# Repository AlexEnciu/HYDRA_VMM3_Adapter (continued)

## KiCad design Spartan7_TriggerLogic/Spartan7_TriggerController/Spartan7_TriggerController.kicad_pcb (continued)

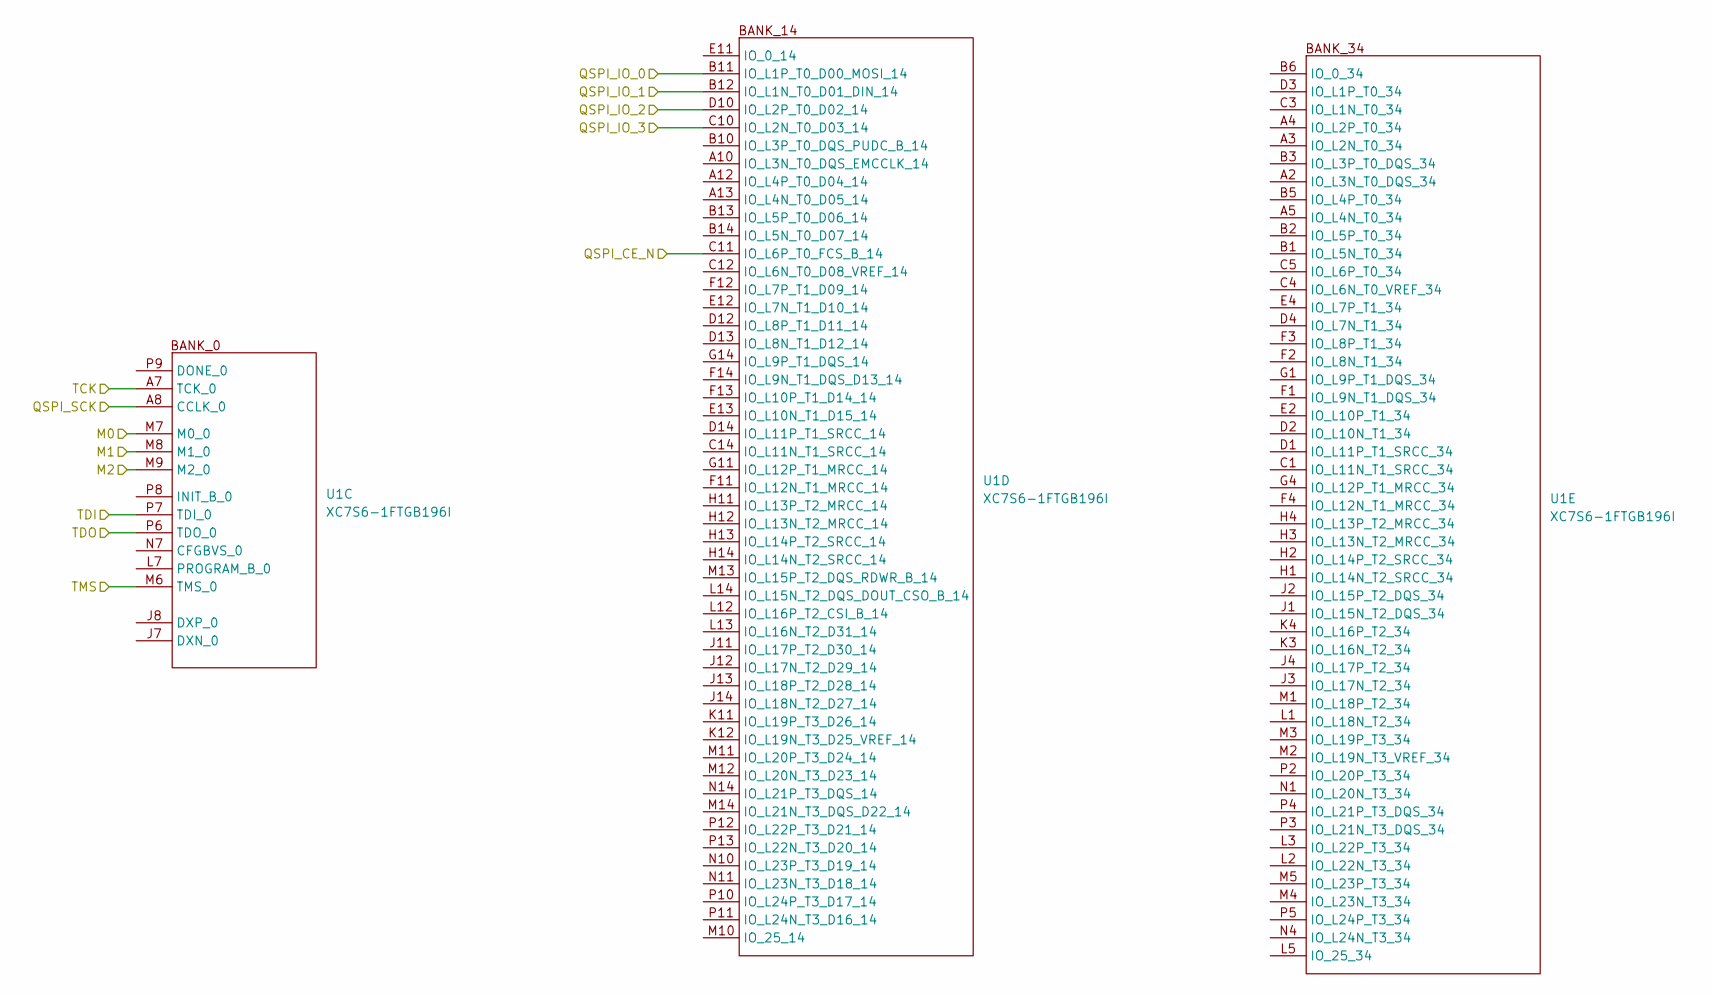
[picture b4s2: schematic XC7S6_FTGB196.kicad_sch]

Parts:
U1: XC7S6-1FTGB196I; BGA196C100P14X14_1500X1500X155N

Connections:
/Boot_Mode/M0: U1.M7 (M0_0); also elsewhere on the board
/Boot_Mode/M1: U1.M8 (M1_0); also elsewhere on the board
/Boot_Mode/M2: U1.M9 (M2_0); also elsewhere on the board
/JTAG/TCK: U1.A7 (TCK_0); also elsewhere on the board
/JTAG/TDI: U1.P7 (TDI_0); also elsewhere on the board
/JTAG/TDO: U1.P6 (TDO_0); also elsewhere on the board
/JTAG/TMS: U1.M6 (TMS_0); also elsewhere on the board
/QSPI/QSPI_CE_N: U1.C11 (IO_L6P_T0_FCS_B_14); also elsewhere on the board
/QSPI/QSPI_IO_0: U1.B11 (IO_L1P_T0_D00_MOSI_14); also elsewhere on the board
/QSPI/QSPI_IO_1: U1.B12 (IO_L1N_T0_D01_DIN_14); also elsewhere on the board
/QSPI/QSPI_IO_2: U1.D10 (IO_L2P_T0_D02_14); also elsewhere on the board
/QSPI/QSPI_IO_3: U1.C10 (IO_L2N_T0_D03_14); also elsewhere on the board
/QSPI/QSPI_SCK: U1.A8 (CCLK_0); also elsewhere on the board

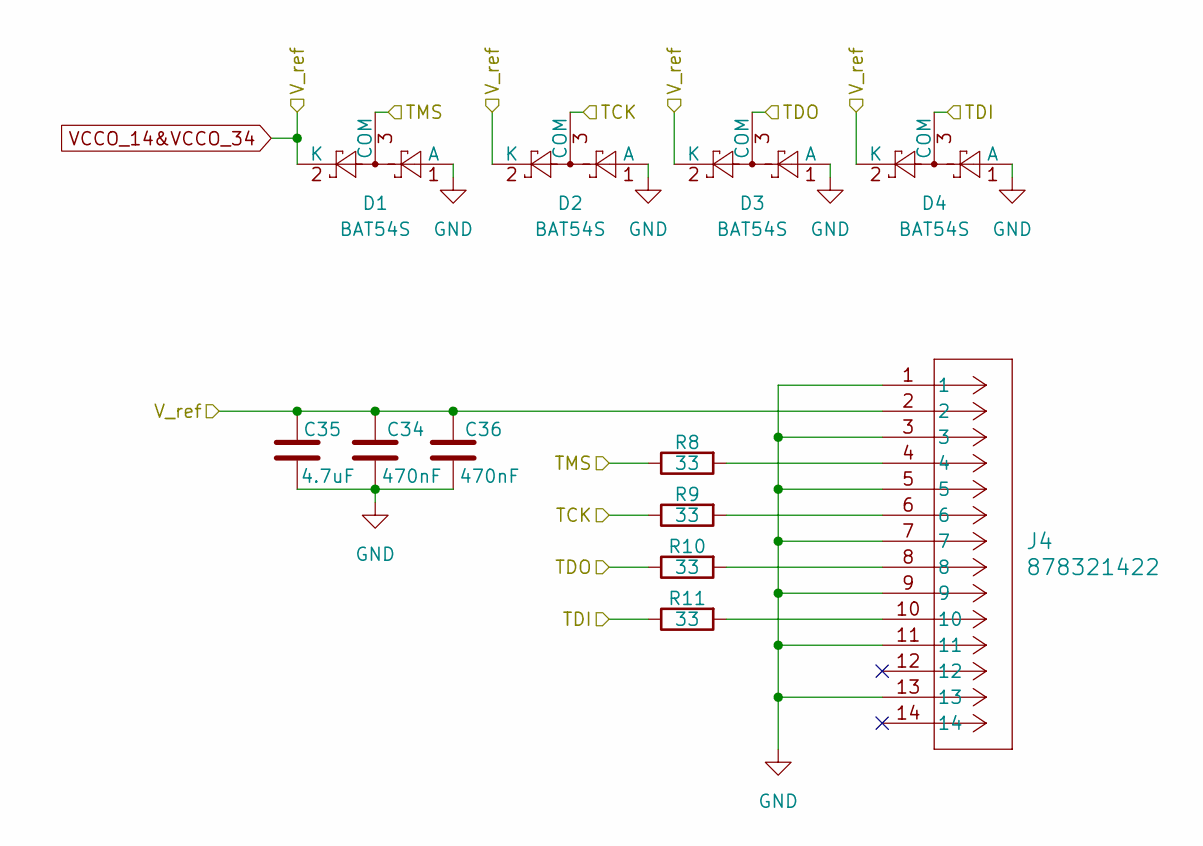
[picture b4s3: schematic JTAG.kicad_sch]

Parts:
C34, C36: 470nF; C_0402_1005Metric
C35: 4.7uF; C_0603_1608Metric
D1, D2, D3, D4: BAT54S; SOT-23
J4: 878321422; CONN14_878321422_MOL
R8, R9, R10, R11: 33; R_0402_1005Metric

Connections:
/JTAG/TCK: D2.3 (COM), R9.1; also elsewhere on the board
/JTAG/TDI: D4.3 (COM), R11.1; also elsewhere on the board
/JTAG/TDO: D3.3 (COM), R10.1; also elsewhere on the board
/JTAG/TMS: D1.3 (COM), R8.1; also elsewhere on the board
GND: C34.2, C35.2, C36.2, D1.1 (A), D2.1 (A), D3.1 (A), D4.1 (A), J4.1, J4.3, J4.5, J4.7, J4.9, J4.11, J4.13; also elsewhere on the board
unnamed: J4.4, R8.2
unnamed: J4.6, R9.2
unnamed: J4.8, R10.2
unnamed: J4.10, R11.2
VCCO_14&VCCO_34: C34.1, C35.1, C36.1, D1.2 (K), D2.2 (K), D3.2 (K), D4.2 (K), J4.2; also elsewhere on the board

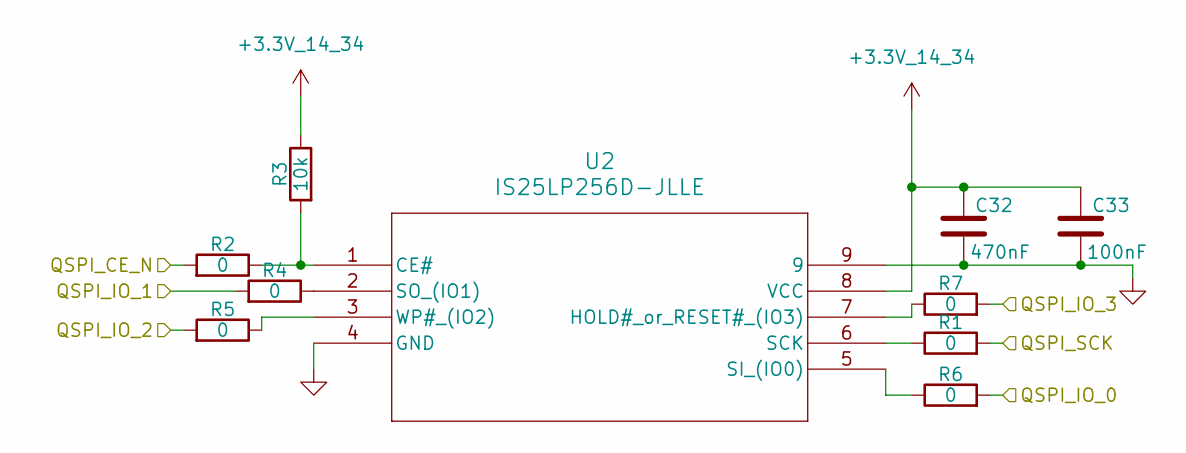
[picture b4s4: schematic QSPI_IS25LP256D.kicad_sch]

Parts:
C32: 470nF; C_0402_1005Metric
C33: 100nF; C_0402_1005Metric
R1, R2, R4, R5, R6, R7: 0; R_0402_1005Metric
R3: 10k; R_0402_1005Metric
U2: IS25LP256D-JLLE; WSON_6D-JLLE_ISI

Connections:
/QSPI/QSPI_CE_N: R2.2; also elsewhere on the board
/QSPI/QSPI_IO_0: R6.2; also elsewhere on the board
/QSPI/QSPI_IO_1: R4.2; also elsewhere on the board
/QSPI/QSPI_IO_2: R5.2; also elsewhere on the board
/QSPI/QSPI_IO_3: R7.2; also elsewhere on the board
/QSPI/QSPI_SCK: R1.2; also elsewhere on the board
GND: C32.2, C33.2, U2.4 (GND), U2.9; also elsewhere on the board
unnamed: R2.1, R3.2, U2.1 (CE#)
unnamed: R7.1, U2.7 (HOLD#_or_RESET#_(IO3))
unnamed: R1.1, U2.6 (SCK)
unnamed: R6.1, U2.5 (SI_(IO0))
unnamed: R4.1, U2.2 (SO_(IO1))
unnamed: R5.1, U2.3 (WP#_(IO2))
VCCO_14&VCCO_34: C32.1, C33.1, R3.1, U2.8 (VCC); also elsewhere on the board

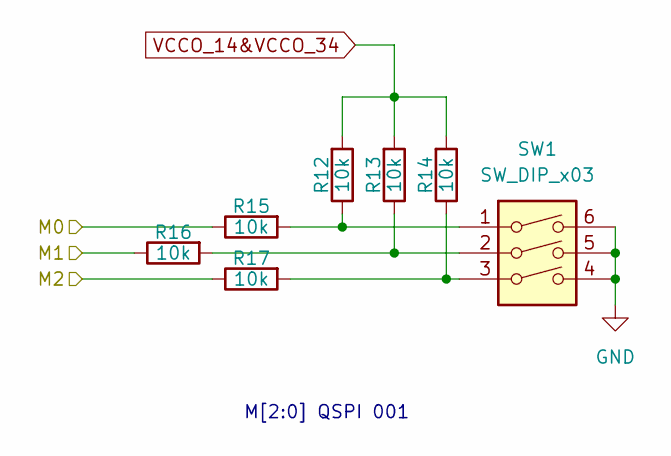
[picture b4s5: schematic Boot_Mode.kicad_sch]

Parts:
R12, R13, R14, R15, R16, R17: 10k; R_0402_1005Metric
SW1: SW_DIP_x03; SW_DIP_SPSTx03_Slide_6.7x9.18mm_W6.73mm_P2.54mm_LowProfile_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

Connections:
/Boot_Mode/M0: R15.1; also elsewhere on the board
/Boot_Mode/M1: R16.1; also elsewhere on the board
/Boot_Mode/M2: R17.1; also elsewhere on the board
GND: SW1.4, SW1.5, SW1.6; also elsewhere on the board
unnamed: R12.1, R15.2, SW1.1
unnamed: R13.1, R16.2, SW1.2
unnamed: R14.1, R17.2, SW1.3
VCCO_14&VCCO_34: R12.2, R13.2, R14.2; also elsewhere on the board

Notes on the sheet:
M[2:0] QSPI 001

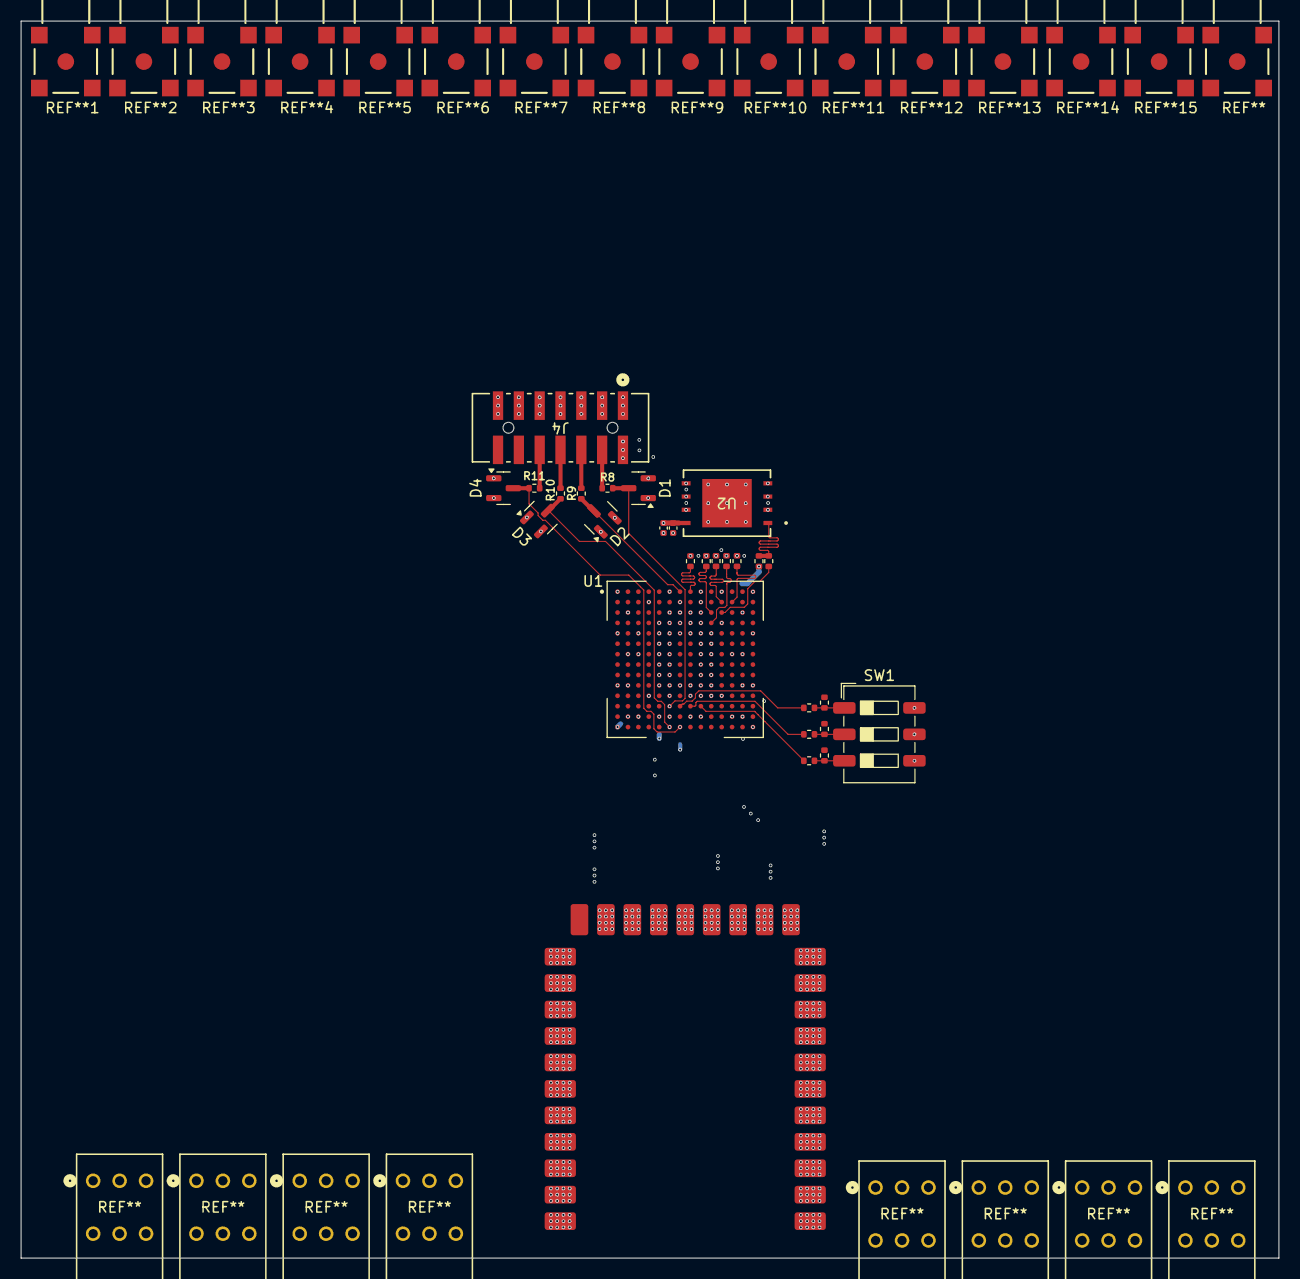
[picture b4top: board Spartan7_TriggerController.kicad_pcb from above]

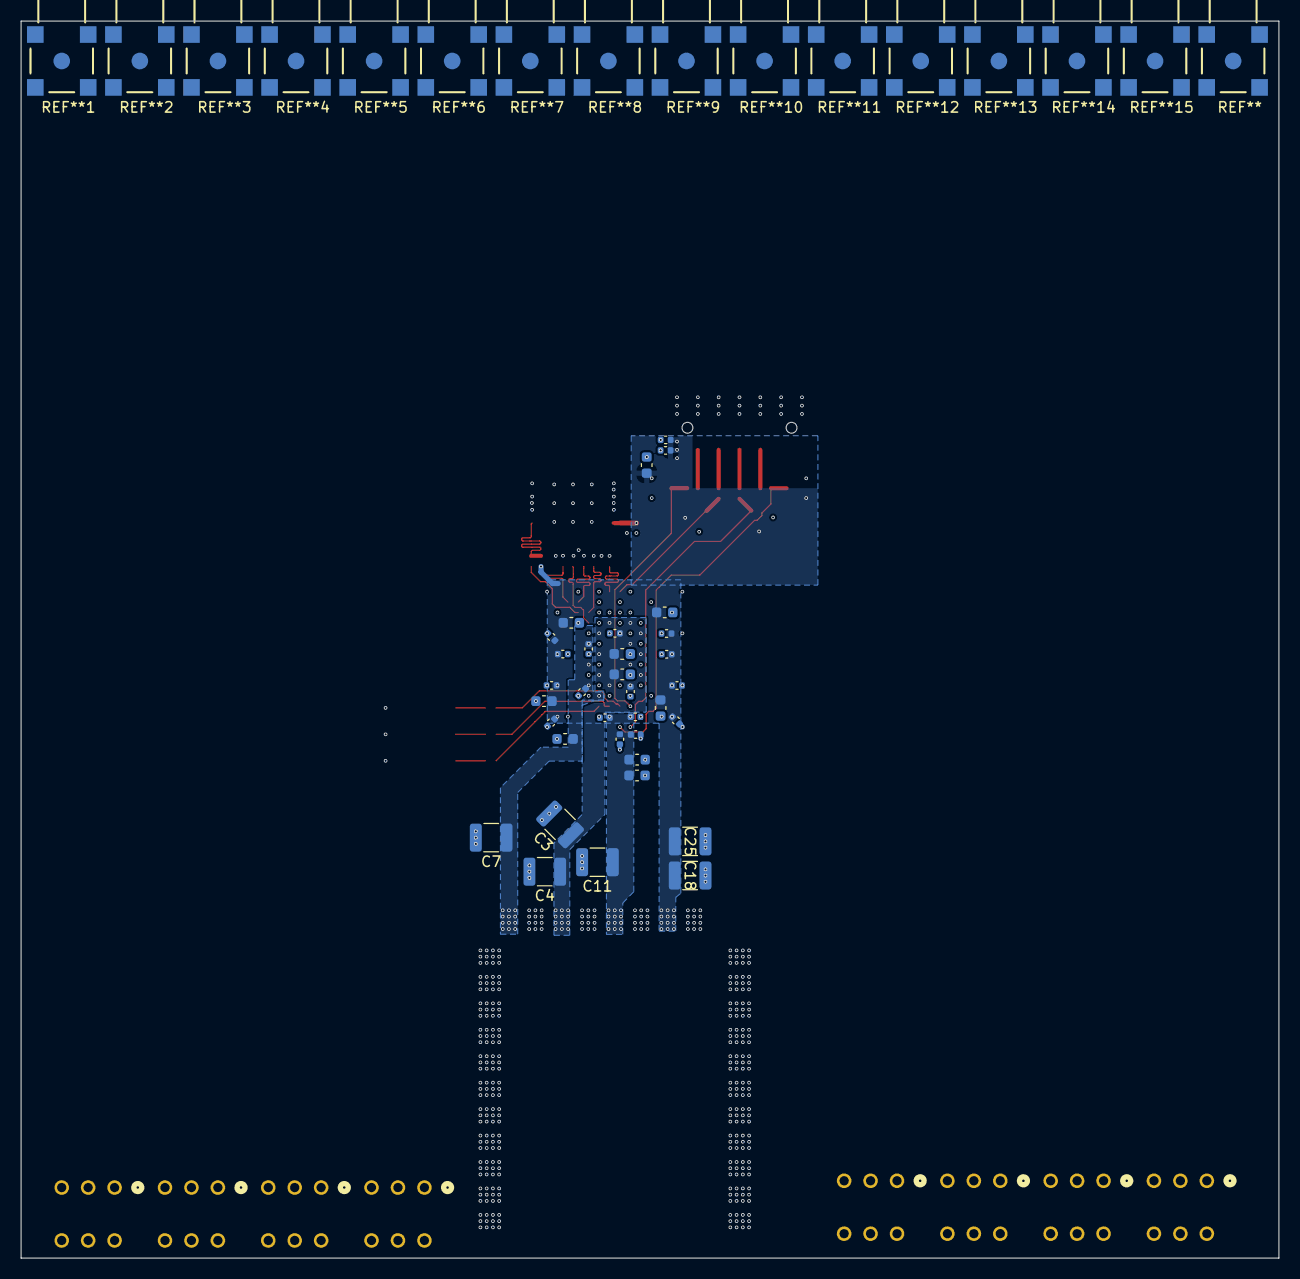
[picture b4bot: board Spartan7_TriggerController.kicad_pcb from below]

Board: 6 copper layers, 120.8 x 118.8 mm, 64 parts (34 on the bottom side), 31 nets.

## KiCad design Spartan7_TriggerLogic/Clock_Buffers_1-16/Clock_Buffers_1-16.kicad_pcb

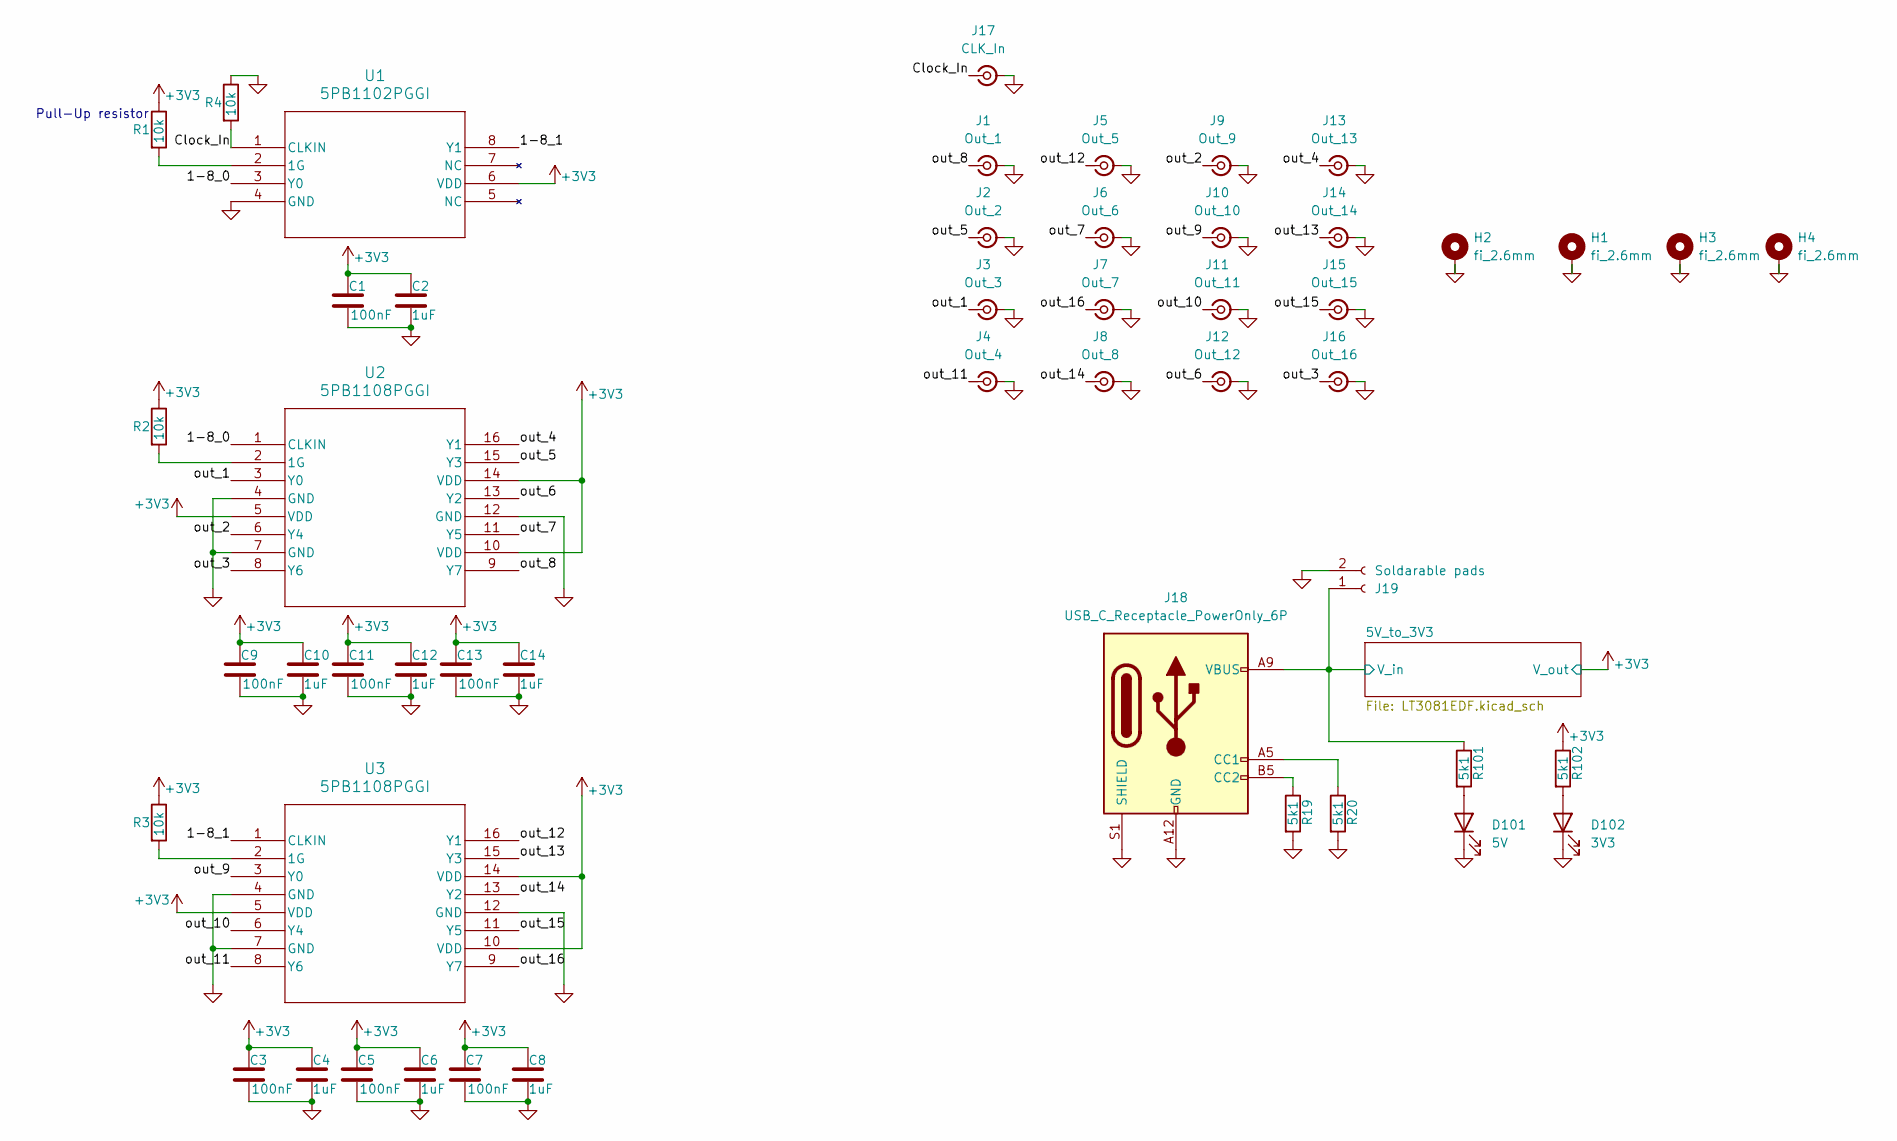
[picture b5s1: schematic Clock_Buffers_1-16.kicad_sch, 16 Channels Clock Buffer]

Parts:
C1, C3, C5, C7, C9, C11, C13: 100nF; C_0402_1005Metric
C2, C4, C6, C8, C10, C12, C14: 1uF; C_0402_1005Metric
D101: 5V; LED_0603_1608Metric
D102: 3V3; LED_0603_1608Metric
H1, H2, H3, H4: fi_2.6mm; MountingHole_2.7mm_M2.5_Pad_Via
J1: Out_1; LINX_CONMCX002-SMD-T
J2: Out_2; LINX_CONMCX002-SMD-T
J3: Out_3; LINX_CONMCX002-SMD-T
J4: Out_4; LINX_CONMCX002-SMD-T
J5: Out_5; LINX_CONMCX002-SMD-T
J6: Out_6; LINX_CONMCX002-SMD-T
J7: Out_7; LINX_CONMCX002-SMD-T
J8: Out_8; LINX_CONMCX002-SMD-T
J9: Out_9; LINX_CONMCX002-SMD-T
J10: Out_10; LINX_CONMCX002-SMD-T
J11: Out_11; LINX_CONMCX002-SMD-T
J12: Out_12; LINX_CONMCX002-SMD-T
J13: Out_13; LINX_CONMCX002-SMD-T
J14: Out_14; LINX_CONMCX002-SMD-T
J15: Out_15; LINX_CONMCX002-SMD-T
J16: Out_16; LINX_CONMCX002-SMD-T
J17: CLK_In; LINX_CONMCX002-SMD-T
J18: USB_C_Receptacle_PowerOnly_6P; CONN6_USB4125_GCT
J19: Soldarable pads; JST_PH_S2B-PH-K_1x02_P2.00mm_Horizontal
R1, R2, R3, R4: 10k; R_0402_1005Metric
R19, R20, R101, R102: 5k1; R_0402_1005Metric
U1: 5PB1102PGGI
U2, U3: 5PB1108PGGI; 5PB1108PGGI_REN

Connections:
+3V3: C1.1, C2.1, C3.1, C4.1, C5.1, C6.1, C7.1, C8.1, C9.1, C10.1, C11.1, C12.1, C13.1, C14.1, R1.1, R2.1, R3.1, R102.1, U1.6 (VDD), U2.5 (VDD), U2.10 (VDD), U2.14 (VDD), U3.5 (VDD), U3.10 (VDD), U3.14 (VDD); also elsewhere on the board
/1-8_0: U1.3 (Y0), U2.1 (CLKIN)
/1-8_1: U1.8 (Y1), U3.1 (CLKIN)
/5V_to_3V3/V_in: J18.A9 (VBUS), J18.B9 (VBUS), J19.1, R101.1; also elsewhere on the board
/Clock_In: J17.1 (In), R4.2, U1.1 (CLKIN)
/out_1: J3.1 (In), U2.3 (Y0)
/out_2: J9.1 (In), U2.6 (Y4)
/out_3: J16.1 (In), U2.8 (Y6)
/out_4: J13.1 (In), U2.16 (Y1)
/out_5: J2.1 (In), U2.15 (Y3)
/out_6: J12.1 (In), U2.13 (Y2)
/out_7: J6.1 (In), U2.11 (Y5)
/out_8: J1.1 (In), U2.9 (Y7)
/out_9: J10.1 (In), U3.3 (Y0)
/out_10: J11.1 (In), U3.6 (Y4)
/out_11: J4.1 (In), U3.8 (Y6)
/out_12: J5.1 (In), U3.16 (Y1)
/out_13: J14.1 (In), U3.15 (Y3)
/out_14: J8.1 (In), U3.13 (Y2)
/out_15: J15.1 (In), U3.11 (Y5)
/out_16: J7.1 (In), U3.9 (Y7)
GND: C1.2, C2.2, C3.2, C4.2, C5.2, C6.2, C7.2, C8.2, C9.2, C10.2, C11.2, C12.2, C13.2, C14.2, D101.1 (K), D102.1 (K), H1.1, H2.1, H3.1, H4.1, J1.2 (Ext), J2.2 (Ext), J3.2 (Ext), J4.2 (Ext), J5.2 (Ext), J6.2 (Ext), J7.2 (Ext), J8.2 (Ext), J9.2 (Ext), J10.2 (Ext), J11.2 (Ext), J12.2 (Ext), J13.2 (Ext), J14.2 (Ext), J15.2 (Ext), J16.2 (Ext), J17.2 (Ext), J18.A12 (GND), J18.B12 (GND), J18.S1 (SHIELD), J19.2, R4.1, R19.2, R20.2, U1.4 (GND), U2.4 (GND), U2.7 (GND), U2.12 (GND), U3.4 (GND), U3.7 (GND), U3.12 (GND); also elsewhere on the board
unnamed: D101.2 (A), R101.2
unnamed: D102.2 (A), R102.2
unnamed: J18.A5 (CC1), R20.1
unnamed: J18.B5 (CC2), R19.1
unnamed: R1.2, U1.2 (1G)
unnamed: R2.2, U2.2 (1G)
unnamed: R3.2, U3.2 (1G)

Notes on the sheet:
Pull-Up resistor

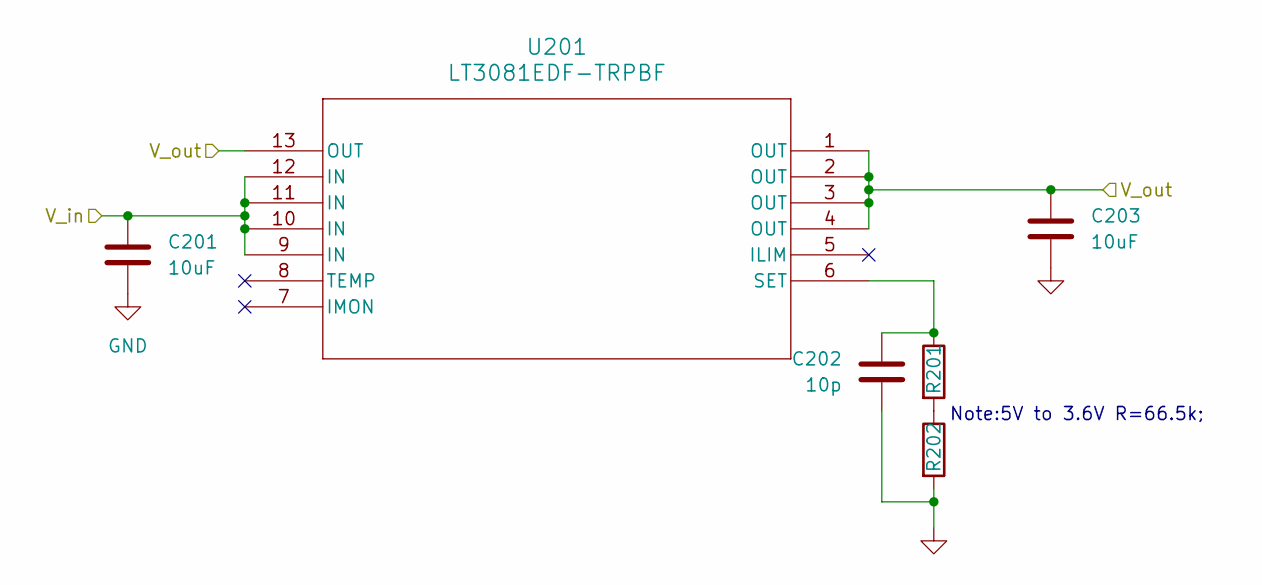
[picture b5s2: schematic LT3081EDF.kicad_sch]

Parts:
C201, C203: 10uF; C_0805_2012Metric
C202: 10p; C_0603_1608Metric
R201, R202: 40k; R_0603_1608Metric
U201: LT3081EDF-TRPBF; DFN-12_DF_LIT

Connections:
+3V3: C203.1, U201.1 (OUT), U201.2 (OUT), U201.3 (OUT), U201.4 (OUT), U201.13 (OUT); also elsewhere on the board
/5V_to_3V3/V_in: C201.1, U201.9 (IN), U201.10 (IN), U201.11 (IN), U201.12 (IN); also elsewhere on the board
GND: C201.2, C202.2, C203.2, R202.2; also elsewhere on the board
unnamed: R201.2, R202.1
unnamed: C202.1, R201.1, U201.6 (SET)

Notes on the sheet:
Note:5V to 3.6V R=66.5k;

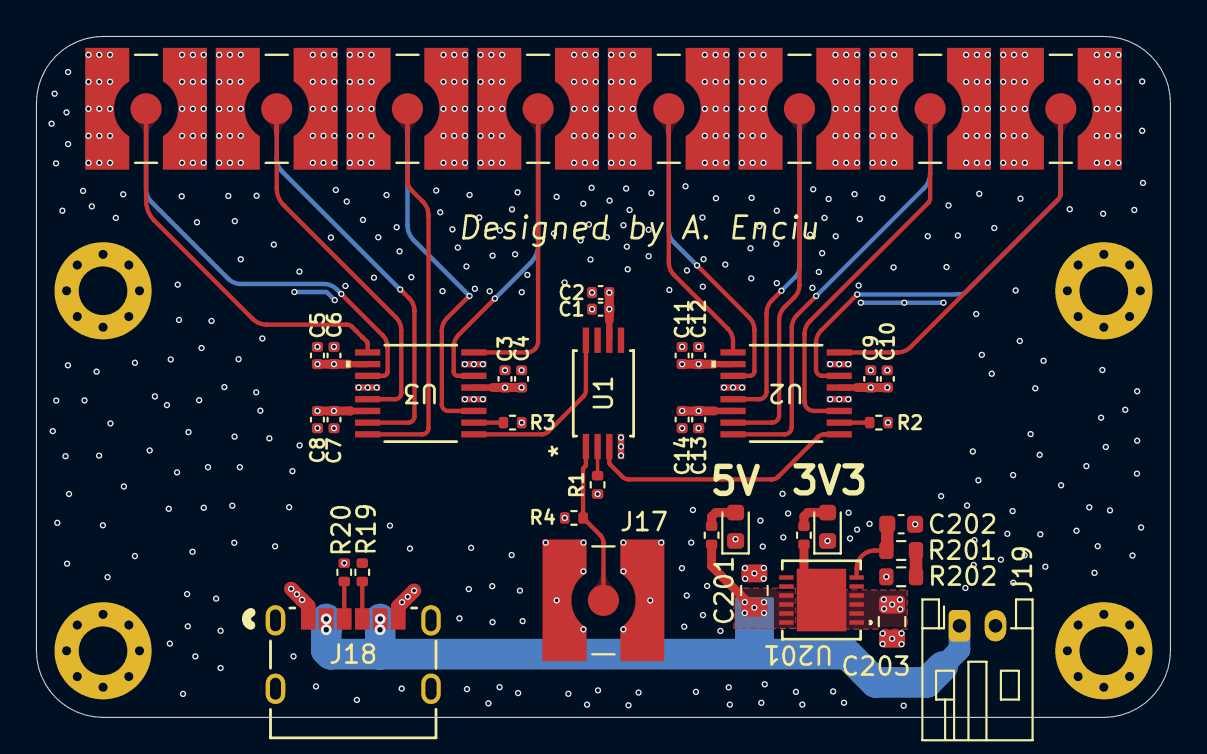
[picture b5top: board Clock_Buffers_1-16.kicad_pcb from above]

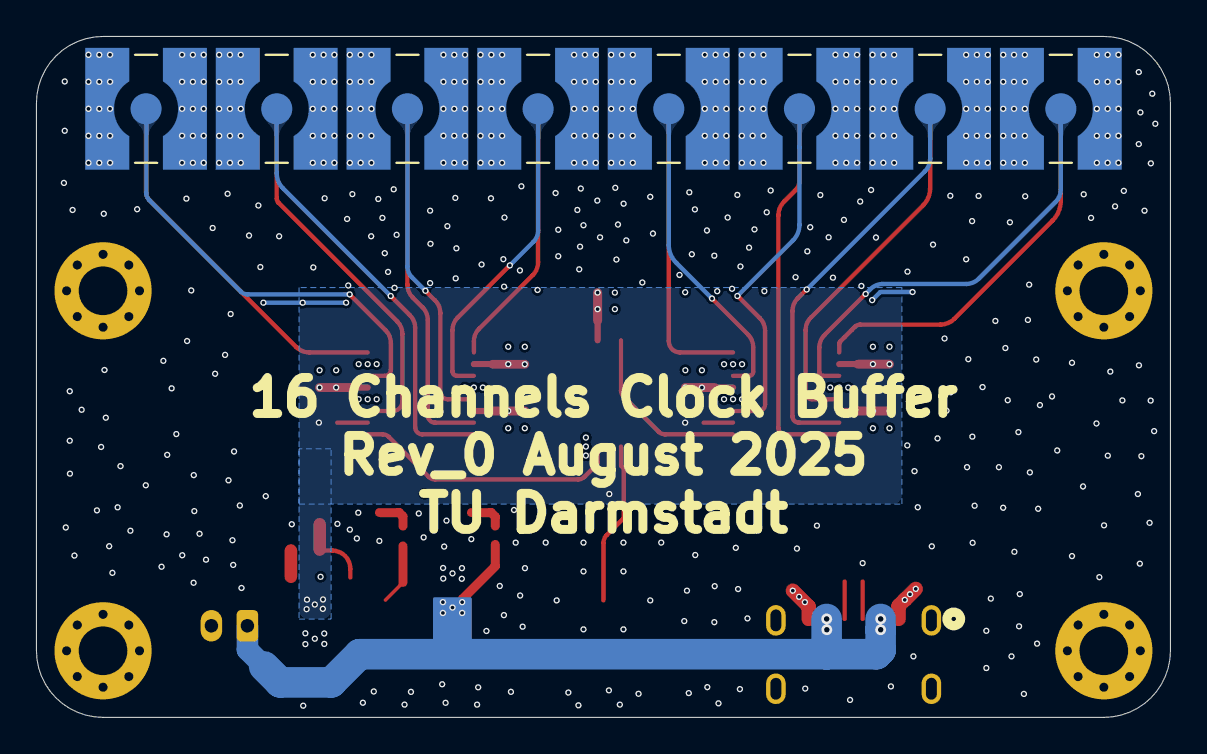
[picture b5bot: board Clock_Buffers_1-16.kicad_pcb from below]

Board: 4 copper layers, 63.0 x 37.8 mm, 56 parts (8 on the bottom side), 31 nets.

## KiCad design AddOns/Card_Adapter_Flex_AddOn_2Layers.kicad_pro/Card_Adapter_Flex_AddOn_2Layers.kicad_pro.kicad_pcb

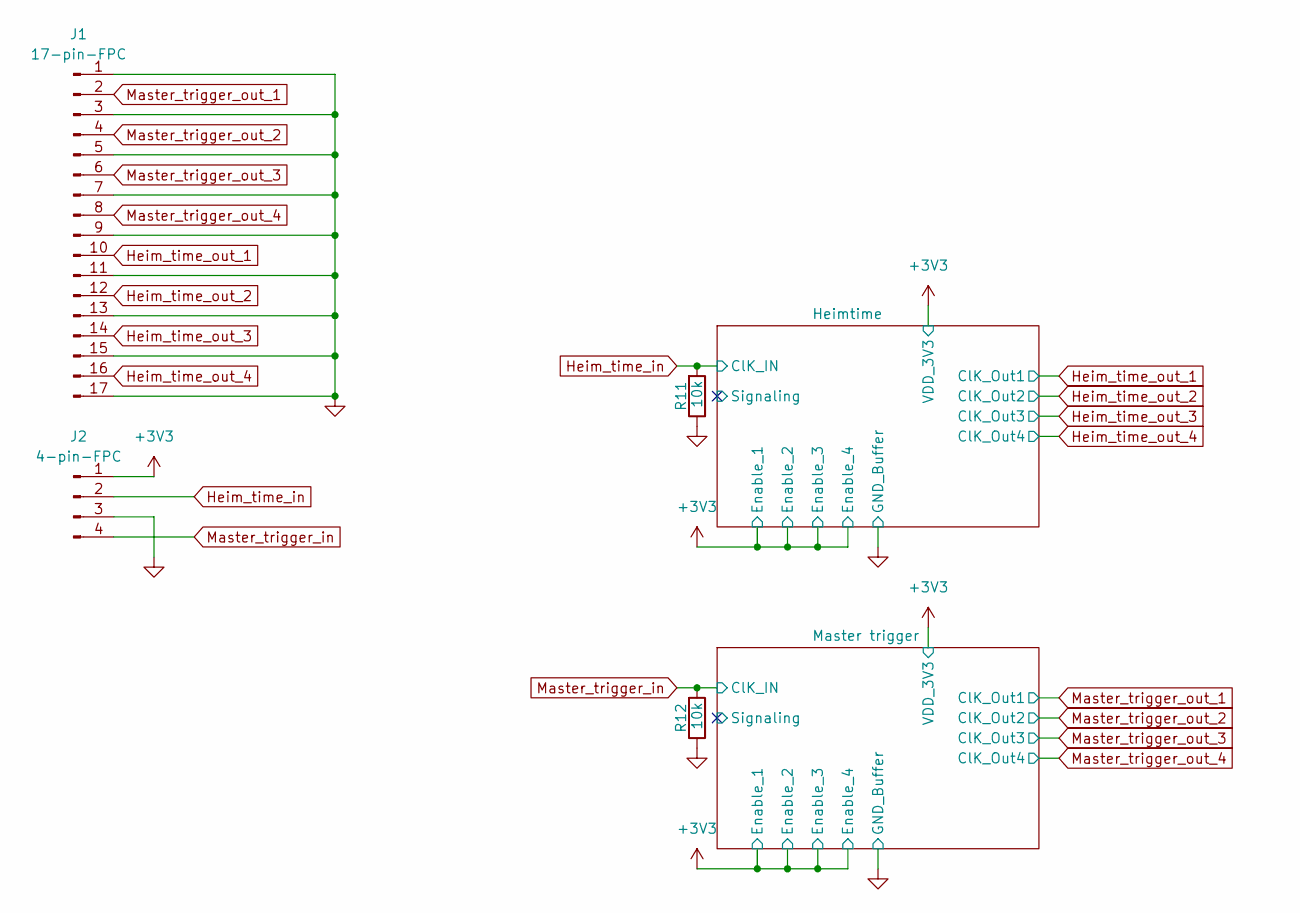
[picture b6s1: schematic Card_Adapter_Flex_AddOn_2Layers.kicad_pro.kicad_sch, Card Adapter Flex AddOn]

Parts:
J1: 17-pin-FPC
J2: 4-pin-FPC
R11, R12: 10k; R_0402_1005Metric

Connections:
+3V3: J2.1; also elsewhere on the board
GND: J1.1, J1.3, J1.5, J1.7, J1.9, J1.11, J1.13, J1.15, J1.17, J2.3, R11.1, R12.1; also elsewhere on the board
Heim_time_in: J2.2, R11.2; also elsewhere on the board
Heim_time_out_1: J1.10; also elsewhere on the board
Heim_time_out_2: J1.12; also elsewhere on the board
Heim_time_out_3: J1.14; also elsewhere on the board
Heim_time_out_4: J1.16; also elsewhere on the board
Master_trigger_in: J2.4, R12.2; also elsewhere on the board
Master_trigger_out_1: J1.2; also elsewhere on the board
Master_trigger_out_2: J1.4; also elsewhere on the board
Master_trigger_out_3: J1.6; also elsewhere on the board
Master_trigger_out_4: J1.8; also elsewhere on the board

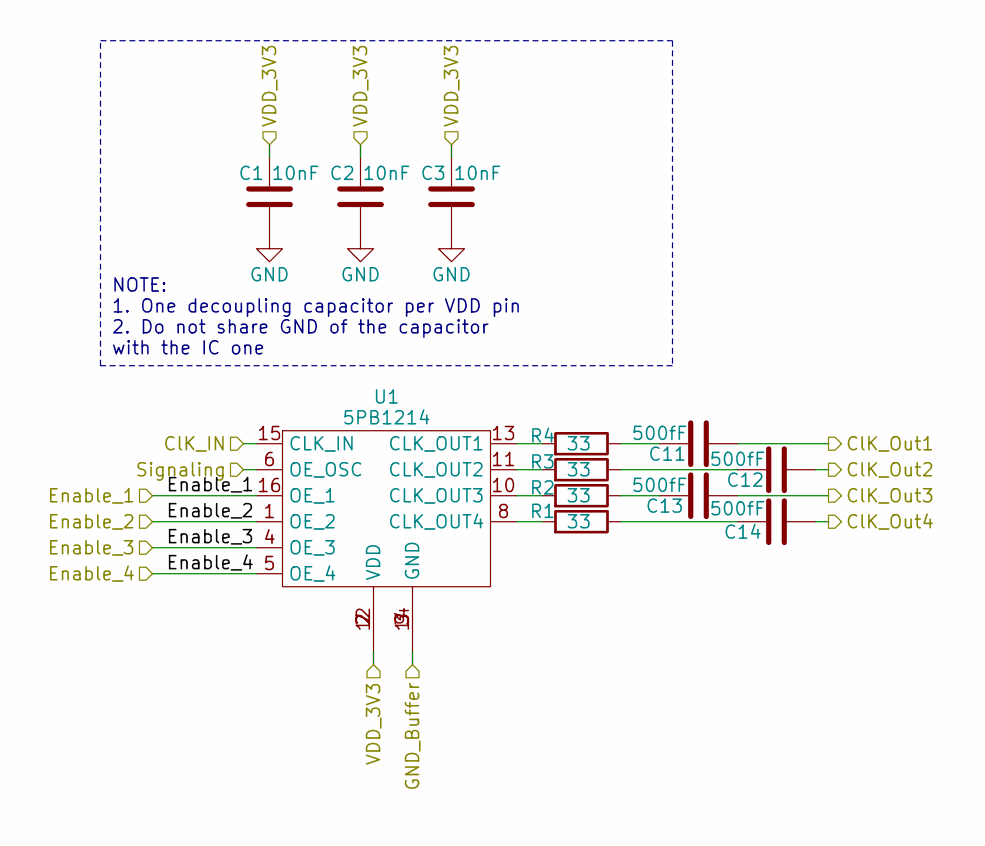
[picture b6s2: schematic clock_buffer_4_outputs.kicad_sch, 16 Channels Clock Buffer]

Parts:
C1, C2, C3: 10nF; C_0402_1005Metric
C11, C12, C13, C14: 500fF; C_0402_1005Metric
R1, R2, R3, R4: 33; R_0402_1005Metric
U1: 5PB1214; 5PB1214CMGK8

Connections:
+3V3: C1.2, C2.2, C3.2, U1.1 (OE_2), U1.2 (VDD), U1.4 (OE_3), U1.5 (OE_4), U1.7 (VDD), U1.12 (VDD), U1.16 (OE_1); also elsewhere on the board
/Heimtime/Signaling: U1.6 (OE_OSC)
GND: C1.1, C2.1, C3.1, U1.3 (GND), U1.9 (GND), U1.14 (GND); also elsewhere on the board
Heim_time_in: U1.15 (CLK_IN); also elsewhere on the board
Heim_time_out_1: C11.1; also elsewhere on the board
Heim_time_out_2: C12.1; also elsewhere on the board
Heim_time_out_3: C13.1; also elsewhere on the board
Heim_time_out_4: C14.1; also elsewhere on the board
unnamed: C11.2, R4.1
unnamed: C12.2, R3.1
unnamed: C13.2, R2.1
unnamed: C14.2, R1.1
unnamed: R4.2, U1.13 (CLK_OUT1)
unnamed: R3.2, U1.11 (CLK_OUT2)
unnamed: R2.2, U1.10 (CLK_OUT3)
unnamed: R1.2, U1.8 (CLK_OUT4)

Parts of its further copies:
C15, C16, C17: 10nF; C_0402_1005Metric
C18, C19, C20, C21: 500fF; C_0402_1005Metric
R13, R14, R15, R16: 33; R_0402_1005Metric
U3: 5PB1214; 5PB1214CMGK8

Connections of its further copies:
+3V3: C15.2, C16.2, C17.2, U3.1 (OE_2), U3.2 (VDD), U3.4 (OE_3), U3.5 (OE_4), U3.7 (VDD), U3.12 (VDD), U3.16 (OE_1); also elsewhere on the board
/Master trigger/Signaling: U3.6 (OE_OSC)
GND: C15.1, C16.1, C17.1, U3.3 (GND), U3.9 (GND), U3.14 (GND); also elsewhere on the board
Master_trigger_in: U3.15 (CLK_IN); also elsewhere on the board
Master_trigger_out_1: C18.1; also elsewhere on the board
Master_trigger_out_2: C19.1; also elsewhere on the board
Master_trigger_out_3: C20.1; also elsewhere on the board
Master_trigger_out_4: C21.1; also elsewhere on the board
unnamed: C18.2, R16.1
unnamed: C19.2, R15.1
unnamed: C20.2, R14.1
unnamed: C21.2, R13.1
unnamed: R16.2, U3.13 (CLK_OUT1)
unnamed: R15.2, U3.11 (CLK_OUT2)
unnamed: R14.2, U3.10 (CLK_OUT3)
unnamed: R13.2, U3.8 (CLK_OUT4)

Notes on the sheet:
NOTE: 1. One decoupling capacitor per VDD pin 2. Do not share GND of the capacitor with the IC one

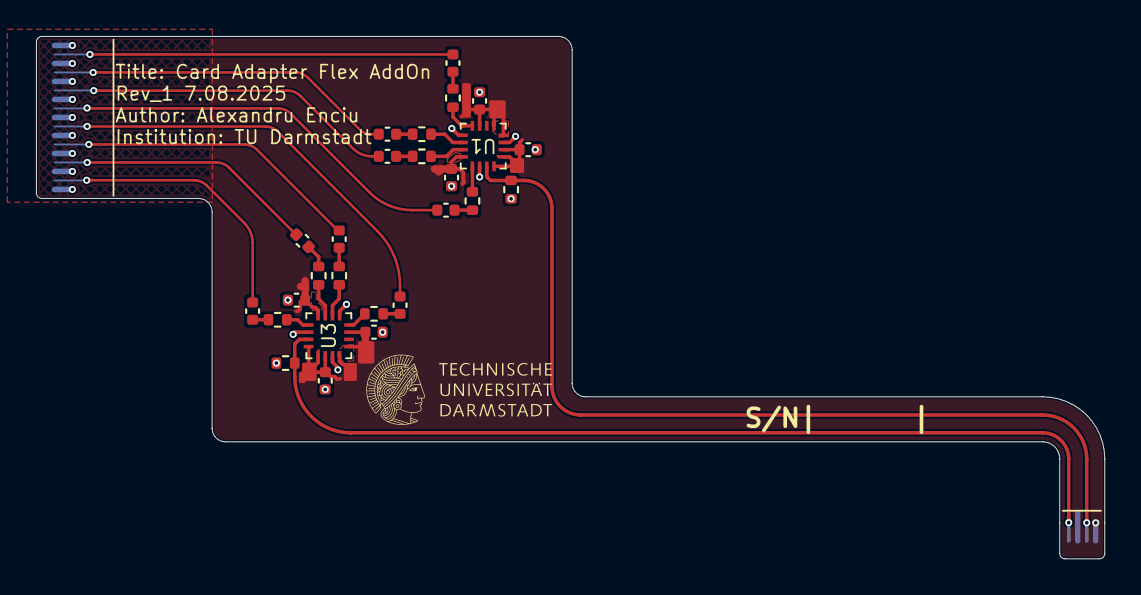
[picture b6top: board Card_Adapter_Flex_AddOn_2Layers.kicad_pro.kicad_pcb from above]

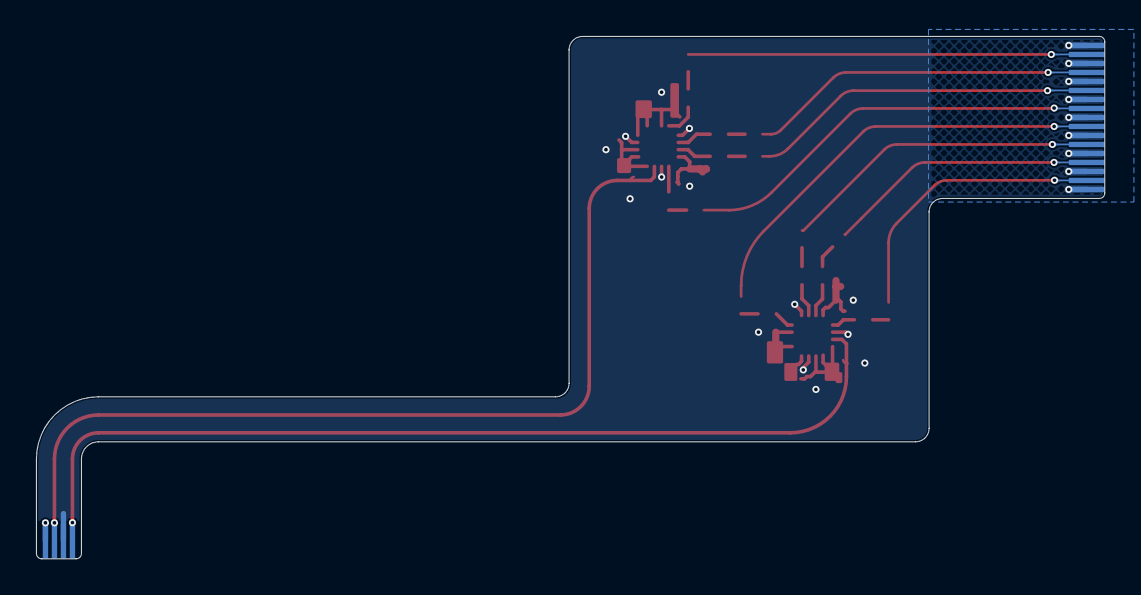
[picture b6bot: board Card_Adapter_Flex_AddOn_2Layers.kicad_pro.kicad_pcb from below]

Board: 2 copper layers, 59.4 x 29.0 mm, 28 parts (2 on the bottom side), 28 nets.
